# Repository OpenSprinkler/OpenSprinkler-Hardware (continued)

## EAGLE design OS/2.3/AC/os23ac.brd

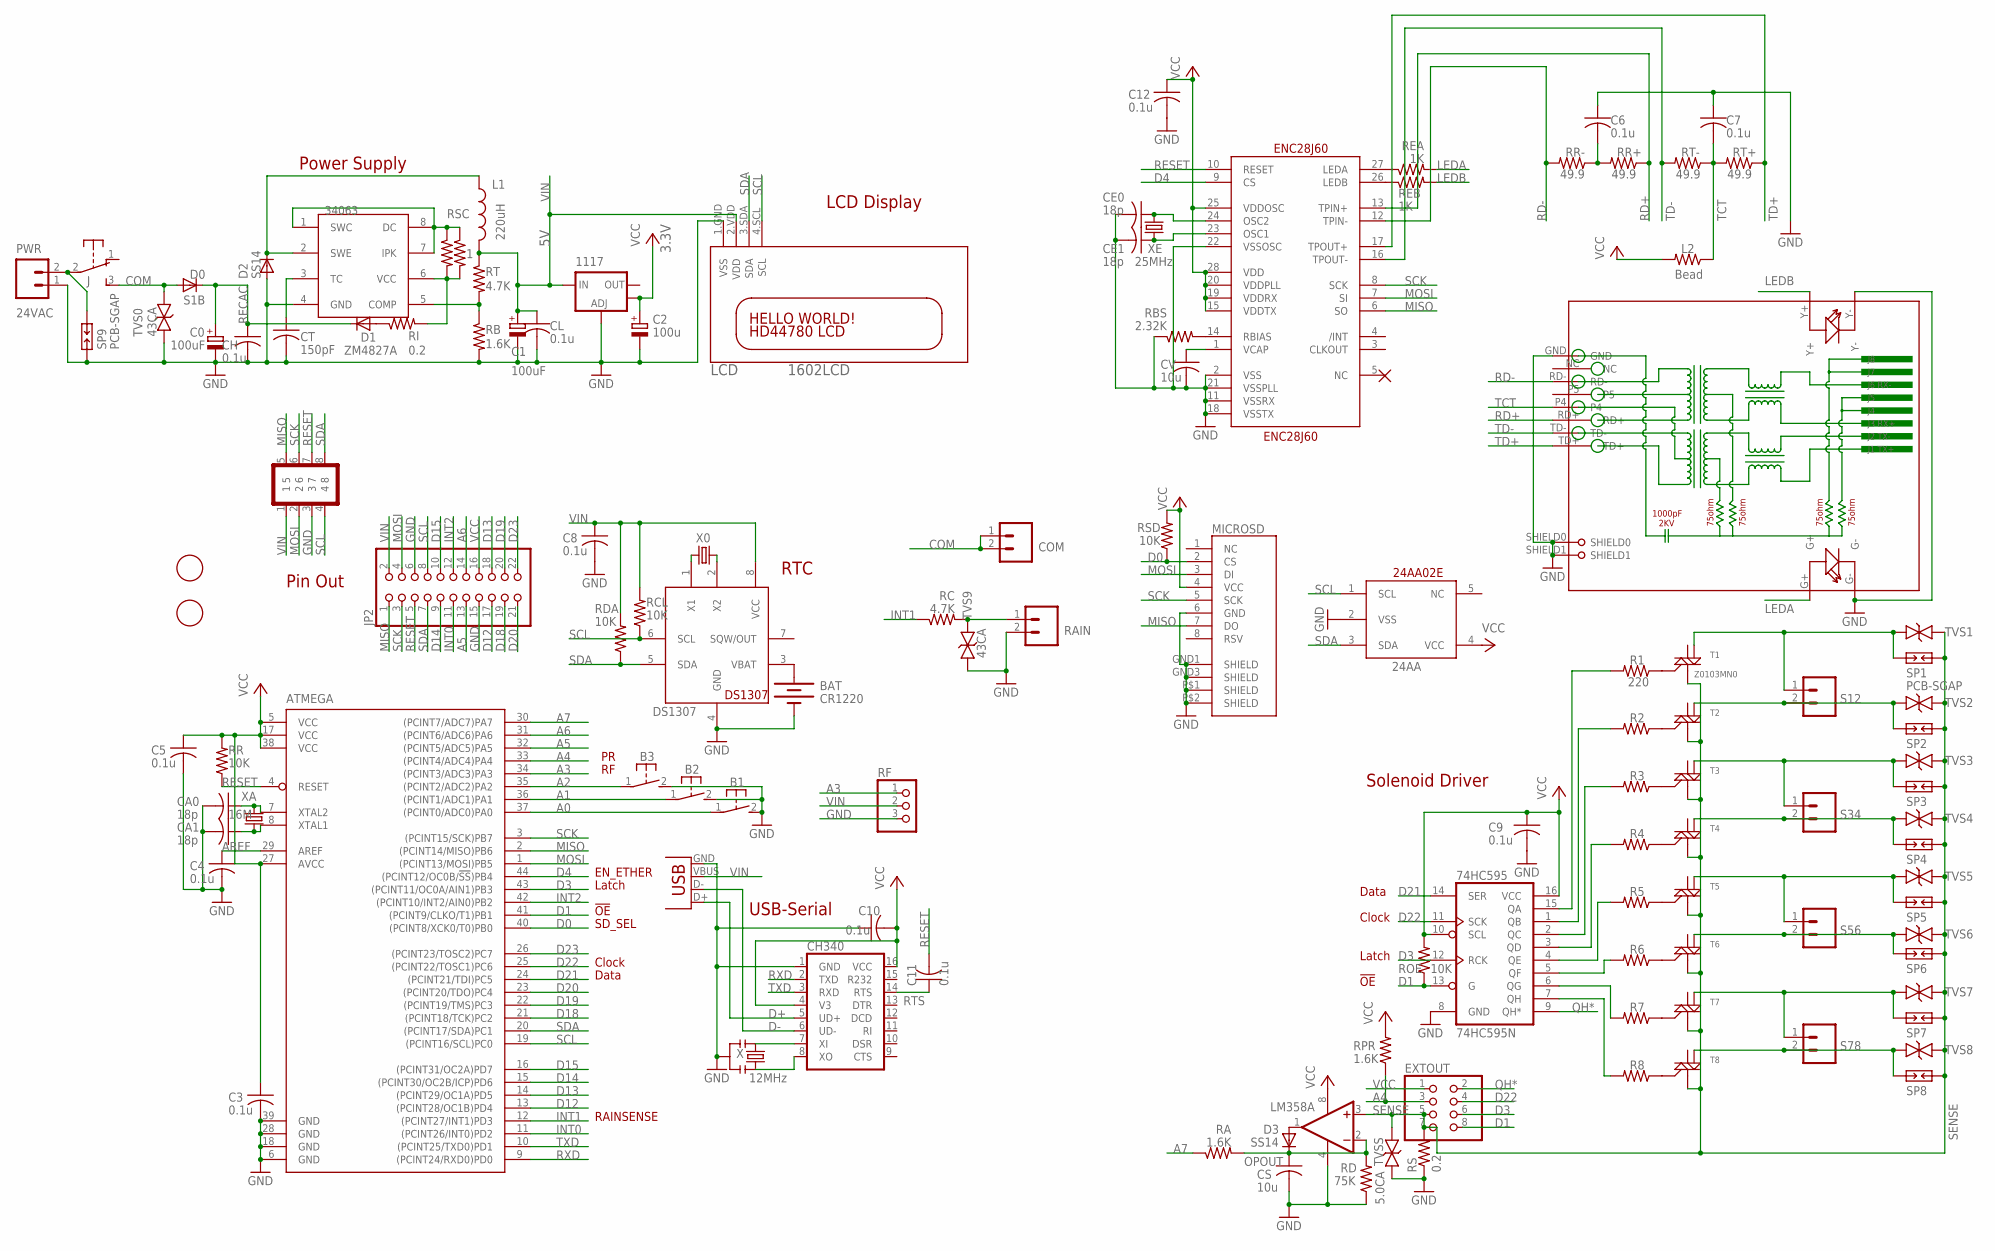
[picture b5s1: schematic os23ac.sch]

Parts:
24AA: 24AA02E48; SOT23-5L
74HC595: 74HC595N; SO16
1117: V_REG_LM1117SOT223; SOT223
34063: 34063; SO08
ATMEGA: ATMEGA644A; TQFP44
B1, B2, B3: 31-XX; B3F-31XX
BAT: CR1220; BATTCON_12MM_SMT
C0: 100uF; PANASONIC_E
C1: 100uF; PANASONIC_D
C2: 100u; PANASONIC_D
C3, C7: 0.1u; C0603K
C4, C5, C6, C8, C9, C10, C11, C12: 0.1u; C0603
CA0, CA1: 18p; C0603K
CE0, CE1: 18p; C0603K
CH: 0.1u; C0603
CH340: CH340G; SO16
CL: 0.1u; C0603
COM: M025MM-X; SCREWTERMINAL-5MM-2-X
CS: 10u; C0805K
CT: 150pF; C0603K
CV: 10u; C0805K
D0: S1B; DO-214AC
D1: ZM4827A; MELF-MLL41
D2, D3: SS14; DO-214AC
DS1307: DS1307; SO08
ENC28J60: ENC28J60SO28LONG; SOIC28WLONG
EXTOUT: PINHD-2X4; 2X04
J: EG1206
JP2: PINHD-2X11; 2X11
L1: 220uH; SRU1038
L2: Bead; R0805
LCD: 1602LCD; LCD1602-I2C-SIDE
LM358: OP262D; SO08
MICROSD: USD-SOCKETMICRO-SD-SOCKET-TAOBAO; MICRO-SD-SOCKET-TAOBAO
PWR: 24VAC; SCREWTERMINAL-4MM-2-X
R1, R2, R3, R4, R5, R6, R7, R8: 220; R0603
RA: 1.6K; R0603
RAIN: M025MM-X; SCREWTERMINAL-5MM-2-X
RB: 1.6K; R0603
RBS: 2.32K; R0805
RC: 4.7K; R0603
RCL: 10K; R0603
RD: 75K; R0603
RDA: 10K; R0603
REA: 1K; R0603
REB: 1K; R0603
RF: PINHD-1X3; 1X03
RI: 0.2; R2512
RJ45: HR911105A
ROE: 10K; R0603
RPR: 1.6K; R0603
RR: 10K; R0603
RR+: 49.9; R0603
RR-: 49.9; R0603
RS: 0.2; R2512
RSC, RSC1: 1; R0805
RSD: 10K; R0603
RT: 4.7K; R0805
RT+: 49.9; R0603
RT-: 49.9; R0603
S12, S34, S56, S78: M025MM-X; SCREWTERMINAL-5MM-2-X
SP1, SP2, SP3, SP4, SP5, SP6, SP7, SP8, SP9: PCB-SGAP
T1: Z0103MN0; SOT223
T2, T3, T4, T5, T6, T7, T8: Z0103MN; SOT223
TVS0, TVS9: 43CA; SMB
TVS1, TVS2, TVS3, TVS4, TVS5, TVS6, TVS7, TVS8: 40CA; SMB
TVSS: 5.0CA; SMB
U$1, U$3: FIDUCIAL; FIDUCIAL_1MM
U$4: GOLDFINGER_2X4
USB: USBPTH; USB-B-PTH
X: 12MHz; RESONATOR-SMD
X0: 32.768kHz; MM20SS
XA: 16M; 4SMD
XE: 25MHz; 4SMD

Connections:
A0: ATMEGA.37 ((PCINT0/ADC0)PA0), B1.1
A1: ATMEGA.36 ((PCINT1/ADC1)PA1), B2.1
A2: ATMEGA.35 ((PCINT2/ADC2)PA2), B3.1
A3: ATMEGA.34 ((PCINT3/ADC3)PA3), RF.1
A4: ATMEGA.33 ((PCINT4/ADC4)PA4), EXTOUT.3, RPR.1
A5: ATMEGA.32 ((PCINT5/ADC5)PA5), JP2.13
A6: ATMEGA.31 ((PCINT6/ADC6)PA6), JP2.14
A7: ATMEGA.30 ((PCINT7/ADC7)PA7), RA.1
AREF: ATMEGA.29 (AREF), C4.1
COM: COM.1, COM.2, D0.A, J.3 (S), TVS0.C
D0: ATMEGA.40 ((PCINT8/XCK0/T0)PB0), MICROSD.2 (CS), RSD.1
D1: 74HC595.13 (G), ATMEGA.41 ((PCINT9/CLKO/T1)PB1), EXTOUT.8, ROE.1
D3: 74HC595.12 (RCK), ATMEGA.43 ((PCINT11/OC0A/AIN1)PB3), EXTOUT.6
D4: ATMEGA.44 ((PCINT12/OC0B/!SS!)PB4), ENC28J60.9 (CS)
D12: ATMEGA.13 ((PCINT28/OC1B)PD4), JP2.17
D13: ATMEGA.14 ((PCINT29/OC1A)PD5), JP2.18
D14: ATMEGA.15 ((PCINT30/OC2B/ICP)PD6), JP2.9
D15: ATMEGA.16 ((PCINT31/OC2A)PD7), JP2.10
D18: ATMEGA.21 ((PCINT18/TCK)PC2), JP2.19
D19: ATMEGA.22 ((PCINT19/TMS)PC3), JP2.20
D20: ATMEGA.23 ((PCINT20/TDO)PC4), JP2.21
D21: 74HC595.14 (SER), ATMEGA.24 ((PCINT21/TDI)PC5)
D22: 74HC595.11 (SCK), ATMEGA.25 ((PCINT22/TOSC1)PC6), EXTOUT.4
D23: ATMEGA.26 ((PCINT23/TOSC2)PC7), JP2.22
D+: CH340.5 (UD+), USB.D+
D-: CH340.6 (UD-), USB.D-
GND: 24AA.2 (VSS), 74HC595.8 (GND), 1117.1 (ADJ), 34063.4 (GND), ATMEGA.6 (GND), ATMEGA.18 (GND), ATMEGA.28 (GND), ATMEGA.39 (GND), B1.2 (S), B2.2 (S), B3.2 (S), BAT.P$1 (-), C0.-, C1.-, C2.-, C3.2, C4.2, C5.2, C6.1, C7.1, C8.2, C9.2, C10.1, C12.2, CA0.2, CA1.2, CE0.2, CE1.2, CH.2, CH340.1 (GND), CL.2, CS.2, CT.2, CV.2, D2.A, DS1307.4 (GND), ENC28J60.2 (VSS), ENC28J60.11 (VSSRX), ENC28J60.18 (VSSTX), ENC28J60.21 (VSSPLL), ENC28J60.22 (VSSOSC), JP2.6, JP2.15, LCD.1.GND (VSS), LM358.4 (V-), MICROSD.6 (GND), MICROSD.GND1 (SHIELD), MICROSD.GND3 (SHIELD), MICROSD.P$1 (SHIELD), MICROSD.P$2 (SHIELD), PWR.1, RAIN.2, RB.2, RBS.1, RD.1, RF.3, RJ45.G-, RJ45.GND, RJ45.SHIELD0, RJ45.SHIELD1, RJ45.Y-, RS.1, SP9.2, TVS0.A, TVS9.A, TVSS.A, U$4.3, USB.GND, X.2
INT0: ATMEGA.11 ((PCINT26/INT0)PD2), JP2.11
INT1: ATMEGA.12 ((PCINT27/INT1)PD3), RC.1
INT2: ATMEGA.42 ((PCINT10/INT2/AIN0)PB2), JP2.12
LEDA: REA.2, RJ45.G+
LEDB: REB.2, RJ45.Y+
MISO: ATMEGA.2 ((PCINT14/MISO)PB6), ENC28J60.6 (SO), JP2.1, MICROSD.7 (DO), U$4.5
MOSI: ATMEGA.1 ((PCINT13/MOSI)PB5), ENC28J60.7 (SI), JP2.4, MICROSD.3 (DI), U$4.2
unnamed: J.2, PWR.2, SP9.1
unnamed: 34063.1 (SWC), 34063.7 (IPK), 34063.8 (DC), RSC.1, RSC1.1
unnamed: RAIN.1, RC.2, TVS9.C
unnamed: 74HC595.5 (QF), R6.2
unnamed: 74HC595.6 (QG), R7.2
unnamed: CH340.7 (XI), X.1
unnamed: 74HC595.7 (QH), R8.2
unnamed: DS1307.1 (X1), X0.1
unnamed: 34063.2 (SWE), D2.C, L1.1
unnamed: 74HC595.4 (QE), R5.2
unnamed: 74HC595.3 (QD), R4.2
unnamed: 74HC595.2 (QC), R3.2
unnamed: 74HC595.1 (QB), R2.2
unnamed: 74HC595.15 (QA), R1.2
unnamed: ATMEGA.7 (XTAL2), CA0.1, XA.1
unnamed: S12.1, SP1.2, T1.4 (M2-4), TVS1.A
unnamed: S12.2, SP2.2, T2.4 (M2-4), TVS2.A
unnamed: S34.1, SP3.2, T3.4 (M2-4), TVS3.A
unnamed: ATMEGA.8 (XTAL1), CA1.1, XA.3 (2)
unnamed: S34.2, SP4.2, T4.4 (M2-4), TVS4.A
unnamed: 34063.3 (TC), CT.1
unnamed: S56.1, SP5.2, T5.4 (M2-4), TVS5.A
unnamed: S56.2, SP6.2, T6.4 (M2-4), TVS6.A
unnamed: S78.1, SP7.2, T7.4 (M2-4), TVS7.A
unnamed: S78.2, SP8.2, T8.4 (M2-4), TVS8.A
unnamed: 34063.6 (VCC), RI.2, RSC.2, RSC1.2
unnamed: D1.A, RI.1
unnamed: R1.1, T1.3 (G)
unnamed: R2.1, T2.3 (G)
unnamed: DS1307.2 (X2), X0.4 (2)
unnamed: R3.1, T3.3 (G)
unnamed: R4.1, T4.3 (G)
unnamed: R5.1, T5.3 (G)
unnamed: ENC28J60.27 (LEDA), REA.1
unnamed: R6.1, T6.3 (G)
unnamed: BAT.P$2 (+), DS1307.3 (VBAT)
unnamed: ENC28J60.26 (LEDB), REB.1
unnamed: R7.1, T7.3 (G)
unnamed: CV.1, ENC28J60.1 (VCAP)
unnamed: CH340.8 (XO), X.3
unnamed: CE0.1, ENC28J60.24 (OSC2), XE.3 (2)
unnamed: CE1.1, ENC28J60.23 (OSC1), XE.1
unnamed: D3.A, LM358.1 (OUT)
unnamed: R8.1, T8.3 (G)
unnamed: C6.2, RR+.2, RR-.1
unnamed: 34063.5 (COMP), RB.1, RT.2
unnamed: ENC28J60.14 (RBIAS), RBS.2
OPOUT: CS.1, D3.C, LM358.2 (-IN), RA.2, RD.2
QH*: 74HC595.9 (QH*), EXTOUT.2
RD+: ENC28J60.13 (TPIN+), RJ45.RD+, RR+.1
RD-: ENC28J60.12 (TPIN-), RJ45.RD-, RR-.2
RECAC: C0.+, CH.1, D0.C, D1.C
RESET: ATMEGA.4 (RESET), C11.2, ENC28J60.10 (RESET), JP2.5, RR.1, U$4.7
RTS: C11.1, CH340.14 (RTS)
RXD: ATMEGA.9 ((PCINT24/RXD0)PD0), CH340.2 (TXD)
SCK: ATMEGA.3 ((PCINT15/SCK)PB7), ENC28J60.8 (SCK), JP2.3, MICROSD.5 (SCK), U$4.6
SCL: 24AA.1 (SCL), ATMEGA.19 ((PCINT16/SCL)PC0), DS1307.6 (SCL), JP2.8, LCD.4.SCL (SCL), RCL.1, U$4.4
SDA: 24AA.3 (SDA), ATMEGA.20 ((PCINT17/SDA)PC1), DS1307.5 (SDA), JP2.7, LCD.3.SDA (SDA), RDA.1, U$4.8
SENSE: EXTOUT.5, EXTOUT.7, LM358.3 (+IN), RS.2, SP1.1, SP2.1, SP3.1, SP4.1, SP5.1, SP6.1, SP7.1, SP8.1, T1.1 (M1), T2.1 (M1), T3.1 (M1), T4.1 (M1), T5.1 (M1), T6.1 (M1), T7.1 (M1), T8.1 (M1), TVS1.C, TVS2.C, TVS3.C, TVS4.C, TVS5.C, TVS6.C, TVS7.C, TVS8.C, TVSS.C
TCT: C7.2, L2.1, RJ45.P4, RT+.2, RT-.1
TD+: ENC28J60.17 (TPOUT+), RJ45.TD+, RT+.1
TD-: ENC28J60.16 (TPOUT-), RJ45.TD-, RT-.2
TXD: ATMEGA.10 ((PCINT25/TXD0)PD1), CH340.3 (RXD)
VCC: 24AA.4 (VCC), 74HC595.10 (SCL), 74HC595.16 (VCC), 1117.4 (OUT), ATMEGA.5 (VCC), ATMEGA.17 (VCC), ATMEGA.27 (AVCC), ATMEGA.38 (VCC), C2.+, C3.1, C5.1, C9.1, C10.2, C12.1, CH340.4 (V3), CH340.16 (VCC), ENC28J60.15 (VDDTX), ENC28J60.19 (VDDRX), ENC28J60.20 (VDDPLL), ENC28J60.25 (VDDOSC), ENC28J60.28 (VDD), EXTOUT.1, JP2.16, L2.2, LM358.8 (V+), MICROSD.4 (VCC), ROE.2, RPR.2, RR.2, RSD.2
VIN: 1117.3 (IN), C1.+, C8.1, CL.1, DS1307.8 (VCC), JP2.2, L1.2, LCD.2.VDD (VDD), RCL.2, RDA.2, RF.2, RT.1, U$4.1, USB.VBUS

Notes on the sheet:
Solenoid Driver
Data
Clock
Latch
EN_ETHER
3.3V
!OE
RAINSENSE
SD_SEL
USB-Serial
Pin Out
RTC
LCD Display
Power Supply

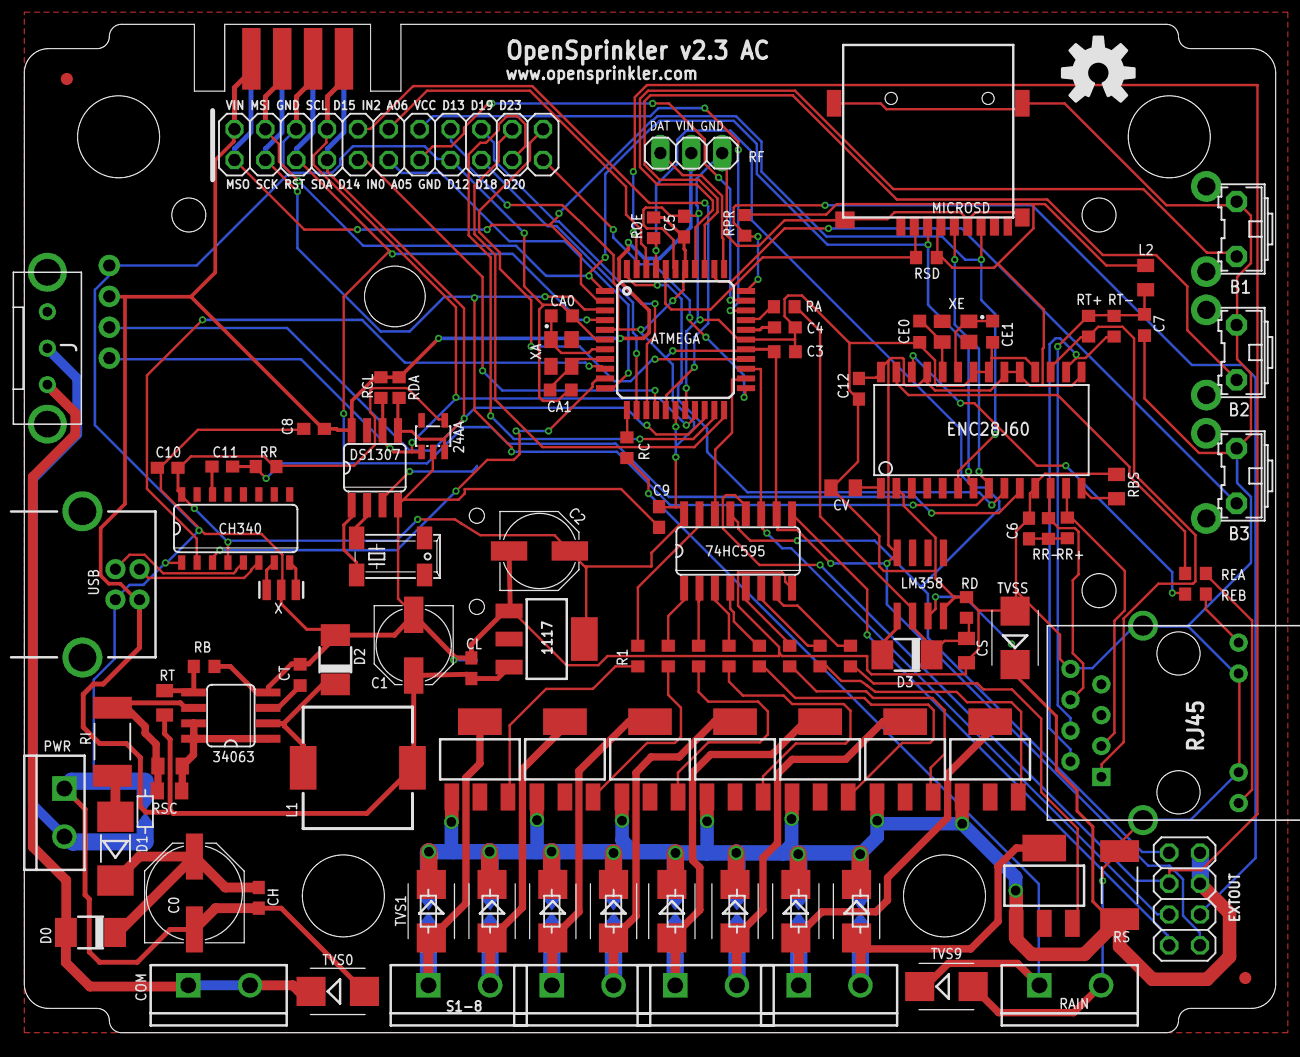
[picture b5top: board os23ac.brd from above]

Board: 2 copper layers, 103.0 x 83.0 mm, 121 parts (1 on the bottom side), 99 nets.
